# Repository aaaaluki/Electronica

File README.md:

# Electronica
Various electronics related projects

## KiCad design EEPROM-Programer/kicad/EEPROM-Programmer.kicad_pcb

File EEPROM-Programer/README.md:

# EEPROM Programmer

## About

The main idea with this project is making the software and hardware necessary for
various operations with an EEPROM (Focused on the AT28C256 and similars).

The operations I want to implement are:
+ Reading (Single address or dump)
+ Writing (Single address or from a .bin file)

To interface with the EEPROM I will use an Arduino Nano and two Shift Registers
(74HC595).

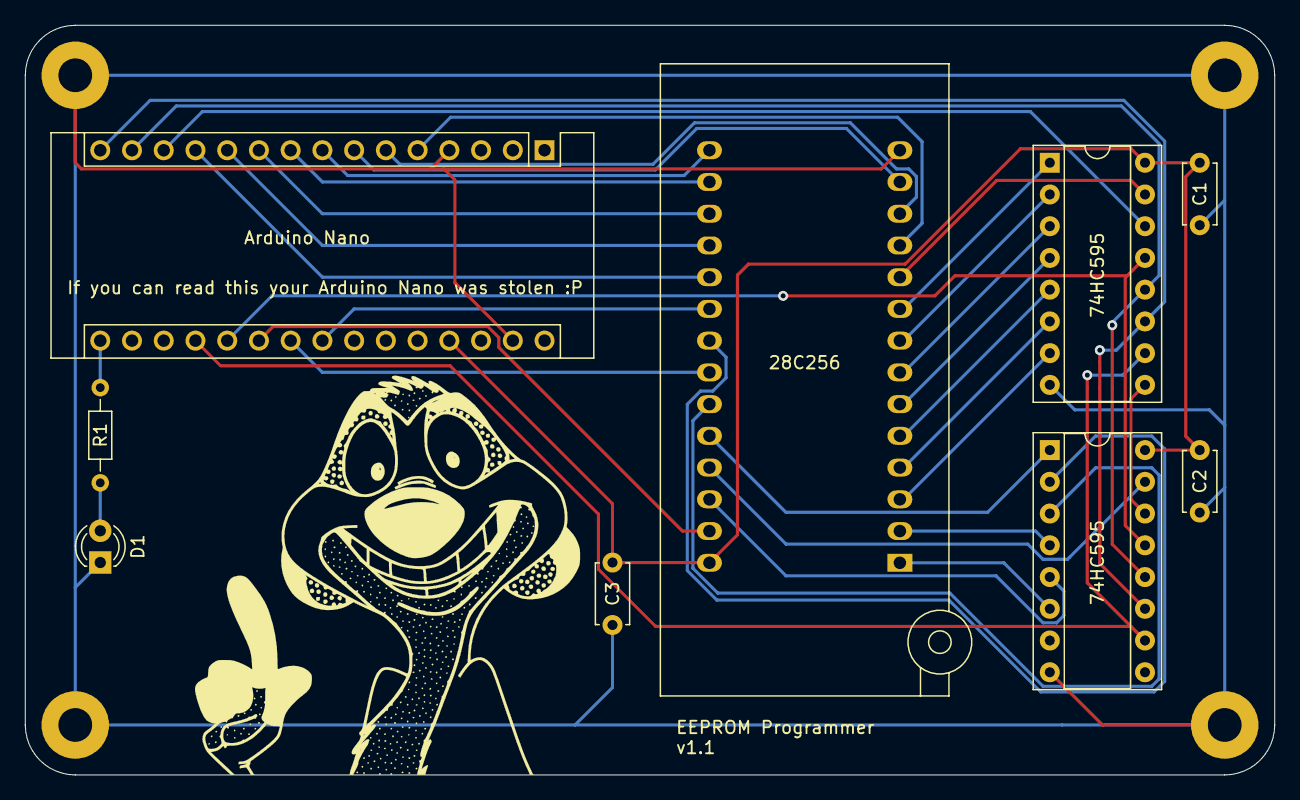
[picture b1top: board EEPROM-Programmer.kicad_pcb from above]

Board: 2 copper layers, 100.0 x 60.0 mm, 14 parts (0 on the bottom side), 36 nets.

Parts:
28C256: 28C256; DIP_Socket-28_W11.9_W12.7_W15.24_W17.78_W18.5_3M_228-1277-0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
74HC595, 74HC595#2: 74HC595; DIP-16_W7.62mm_Socket
Arduino Nano: Arduino_Nano_v3.x; Arduino_Nano
C1, C2, C3: 100n; C_Disc_D4.7mm_W2.5mm_P5.00mm
D1: LED; LED_D3.0mm
H1, H2, H3, H4: MountingHole_Pad; MountingHole_2.7mm_Pad
R1: 220; R_Axial_DIN0204_L3.6mm_D1.6mm_P7.62mm_Horizontal
Timon: LOGO; timon_31x32

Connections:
GND: 28C256.14, 74HC595.8, 74HC595#2.8, Arduino Nano.4, Arduino Nano.29, C1.1, C2.1, C3.1, D1.1, H1.1, H2.1, H3.1, H4.1
unnamed: 28C256.11, Arduino Nano.5
unnamed: 28C256.12, Arduino Nano.6
unnamed: 28C256.13, Arduino Nano.7
unnamed: 28C256.15, Arduino Nano.8
unnamed: 28C256.16, Arduino Nano.9
unnamed: 28C256.17, Arduino Nano.10
unnamed: 28C256.18, Arduino Nano.11
unnamed: 28C256.19, Arduino Nano.12
unnamed: 74HC595.14, Arduino Nano.13
unnamed: 74HC595.12, 74HC595#2.12, Arduino Nano.14
unnamed: 74HC595.11, 74HC595#2.11, Arduino Nano.15
unnamed: Arduino Nano.16, R1.1
unnamed: 74HC595.10, 74HC595#2.10, Arduino Nano.19
unnamed: 74HC595.13, 74HC595#2.13, Arduino Nano.20
unnamed: 28C256.27, Arduino Nano.21
unnamed: 28C256.22, Arduino Nano.22
unnamed: 28C256.20, Arduino Nano.23
unnamed: D1.2, R1.2
unnamed: 28C256.9, 74HC595.1
unnamed: 28C256.8, 74HC595.2
unnamed: 28C256.7, 74HC595.3
unnamed: 28C256.6, 74HC595.4
unnamed: 28C256.5, 74HC595.5
unnamed: 28C256.4, 74HC595.6
unnamed: 28C256.3, 74HC595.7
unnamed: 74HC595.9, 74HC595#2.14
unnamed: 28C256.10, 74HC595.15
unnamed: 28C256.24, 74HC595#2.1
unnamed: 28C256.21, 74HC595#2.2
unnamed: 28C256.23, 74HC595#2.3
unnamed: 28C256.2, 74HC595#2.4
unnamed: 28C256.26, 74HC595#2.5
unnamed: 28C256.1, 74HC595#2.6
unnamed: 28C256.25, 74HC595#2.15
Vcc: 28C256.28, 74HC595.16, 74HC595#2.16, Arduino Nano.27, C1.2, C2.2, C3.2

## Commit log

2021-08-02 Added .gitignore for KiCad
    gitignore file for KiCad projects
2021-08-02 List of interesting components I find
2021-08-02 Arbre Nadal: Finished project
    I was repairing a PCB of a christmas tree I found, this is the
    schematic.
2021-08-02 "Logos" to add to the PCBs
    Added an image of timon for putting it to the pcbs. The file is in
    different formats for convenience.
2021-08-02 EEPROM Programmer: First idea
    This project is focused on making an EEPROM programmer. Also this should
    read and write the EEPROM.
2021-08-02 EEPROM Programmer: Added README.md file
2021-08-06 Renamed personal library
2021-08-06 EEPROM Programmer: New circuit, with more flexibility
    Redesigned the circuit to be able to control the OE, CS and WE pins from the
    EEPROM, and the OE, SRCLR pins from the shift register.
    This gives us more total control of all the pins in both chips, and
    enables us to write to the EEPROM (before the WE pin was always HIGH).
    I also added a status LED for monitoring.
